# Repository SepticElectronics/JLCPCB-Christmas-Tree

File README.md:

# JLCPCB-Christmas-Tree

This is my entry for the JLCPCB.com Christmas Challenge.

It is a PCB christmas tree assembled from three separate PCBs: one for the Top, on as a spacer and one as the backside.
They are held together by soldering with solder paste on the inside and a hole for a string at the top.

On the inside, there are multiple sideview LEDs to illuminate the edge of the tree. To reduce current consumption, all LEDs are pulse-width-modulated by a PIC16F18344.

The other LEDs are normal topview LEDs, placed on both the top and the bottom side of the tree, which illuminate the tree decorations of the opposing PCB. These LEDs are multiplexed by the MCU, to enable different flashing modes.
These modes are selected by a very simple touch-sensor, built into the main PCB.

Power is supplied by a CR1216-cell, held between the PCBs by friction with SMD-resistors to hold it in position. 

A TPS61260 steps up the battery voltage to 3.3 V.

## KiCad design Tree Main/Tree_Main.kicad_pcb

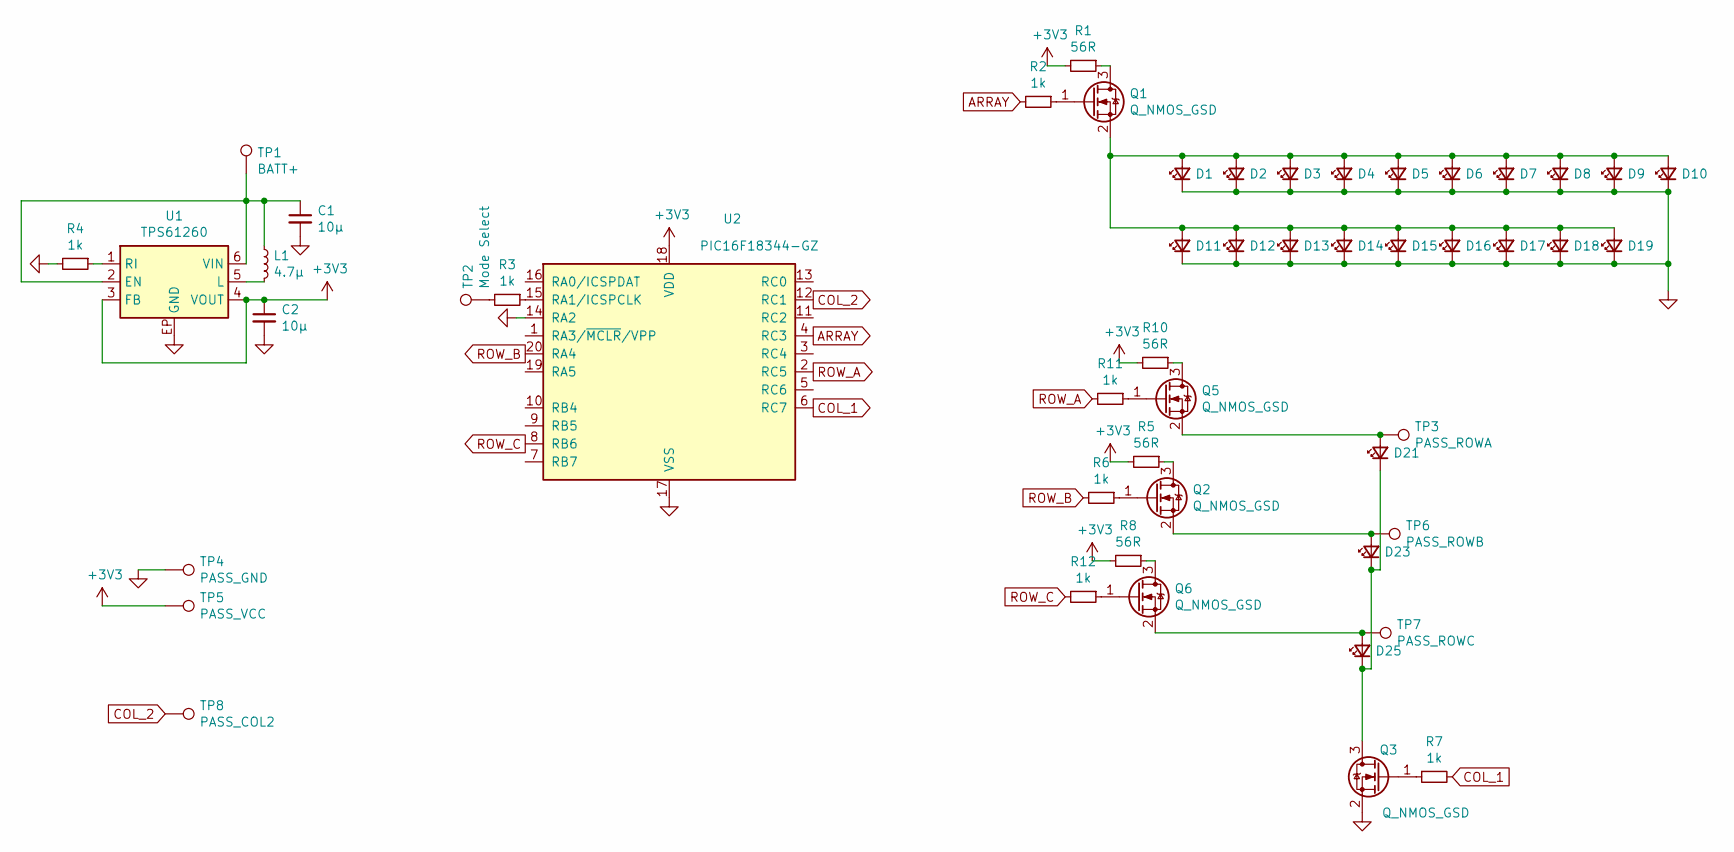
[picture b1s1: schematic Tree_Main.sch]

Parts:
C1, C2: 10µ; C_0603_1608Metric
D1, D2, D3, D4, D5, D6, D7, D8, D9, D10, D11, D12, D13, D14, D15, D16, D17, D18, D19, D21, D23, D25: LED_Small; LED_0603_1608Metric
L1: 4.7µ; L_0805_2012Metric
Q1, Q2, Q3, Q5, Q6: Q_NMOS_GSD; SOT-23
R1, R5, R8, R10: 56R; R_0603_1608Metric
R2, R3, R4, R6, R7, R11, R12: 1k; R_0603_1608Metric
TP1: BATT+; TestPoint_Pad_D4.0mm
TP2: Mode Select; TestPoint_Pad_D4.0mm
TP3: PASS_ROWA; TestPoint_Pad_D1.0mm
TP4: PASS_GND; TestPoint_Pad_D1.0mm
TP5: PASS_VCC; TestPoint_Pad_D1.0mm
TP6: PASS_ROWB; TestPoint_Pad_D1.0mm
TP7: PASS_ROWC; TestPoint_Pad_D1.0mm
TP8: PASS_COL2; TestPoint_Pad_D1.0mm
U1: TPS61260; WSON-6-1EP_2x2mm_P0.65mm_EP1x1.6mm
U2: PIC16F18344-GZ; UQFN-20-1EP_4x4mm_P0.5mm_EP2.8x2.8mm

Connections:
+3V3: C2.1, R1.2, R5.2, R8.2, R10.2, TP5.1, U1.3 (FB), U1.4 (VOUT), U2.18 (VDD)
ARRAY: R2.2, U2.4 (RC3)
COL_1: R7.2, U2.6 (RC7)
COL_2: TP8.1, U2.12 (RC1)
GND: C1.2, C2.2, D1.1 (K), D2.1 (K), D3.1 (K), D4.1 (K), D5.1 (K), D6.1 (K), D7.1 (K), D8.1 (K), D9.1 (K), D10.1 (K), D11.1 (K), D12.1 (K), D13.1 (K), D14.1 (K), D15.1 (K), D16.1 (K), D17.1 (K), D18.1 (K), D19.1 (K), Q3.2 (S), R4.2, TP4.1, U1.EP (GND), U2.14 (RA2), U2.17 (VSS)
unnamed: C1.1, L1.1, TP1.1, U1.2 (EN), U1.6 (VIN)
unnamed: D1.2 (A), D2.2 (A), D3.2 (A), D4.2 (A), D5.2 (A), D6.2 (A), D7.2 (A), D8.2 (A), D9.2 (A), D10.2 (A), D11.2 (A), D12.2 (A), D13.2 (A), D14.2 (A), D15.2 (A), D16.2 (A), D17.2 (A), D18.2 (A), D19.2 (A), Q1.2 (S)
unnamed: D21.2 (A), Q5.2 (S), TP3.1
unnamed: D21.1 (K), D23.1 (K), D25.1 (K), Q3.3 (D)
unnamed: D23.2 (A), Q2.2 (S), TP6.1
unnamed: D25.2 (A), Q6.2 (S), TP7.1
unnamed: L1.2, U1.5 (L)
unnamed: Q1.1 (G), R2.1
unnamed: Q1.3 (D), R1.1
unnamed: Q2.1 (G), R6.1
unnamed: Q2.3 (D), R5.1
unnamed: Q3.1 (G), R7.1
unnamed: Q5.1 (G), R11.1
unnamed: Q5.3 (D), R10.1
unnamed: Q6.1 (G), R12.1
unnamed: Q6.3 (D), R8.1
unnamed: R3.1, U2.15 (RA1/ICSPCLK)
unnamed: R3.2, TP2.1
unnamed: R4.1, U1.1 (RI)
ROW_A: R11.2, U2.2 (RC5)
ROW_B: R6.2, U2.20 (RA4)
ROW_C: R12.2, U2.8 (RB6)

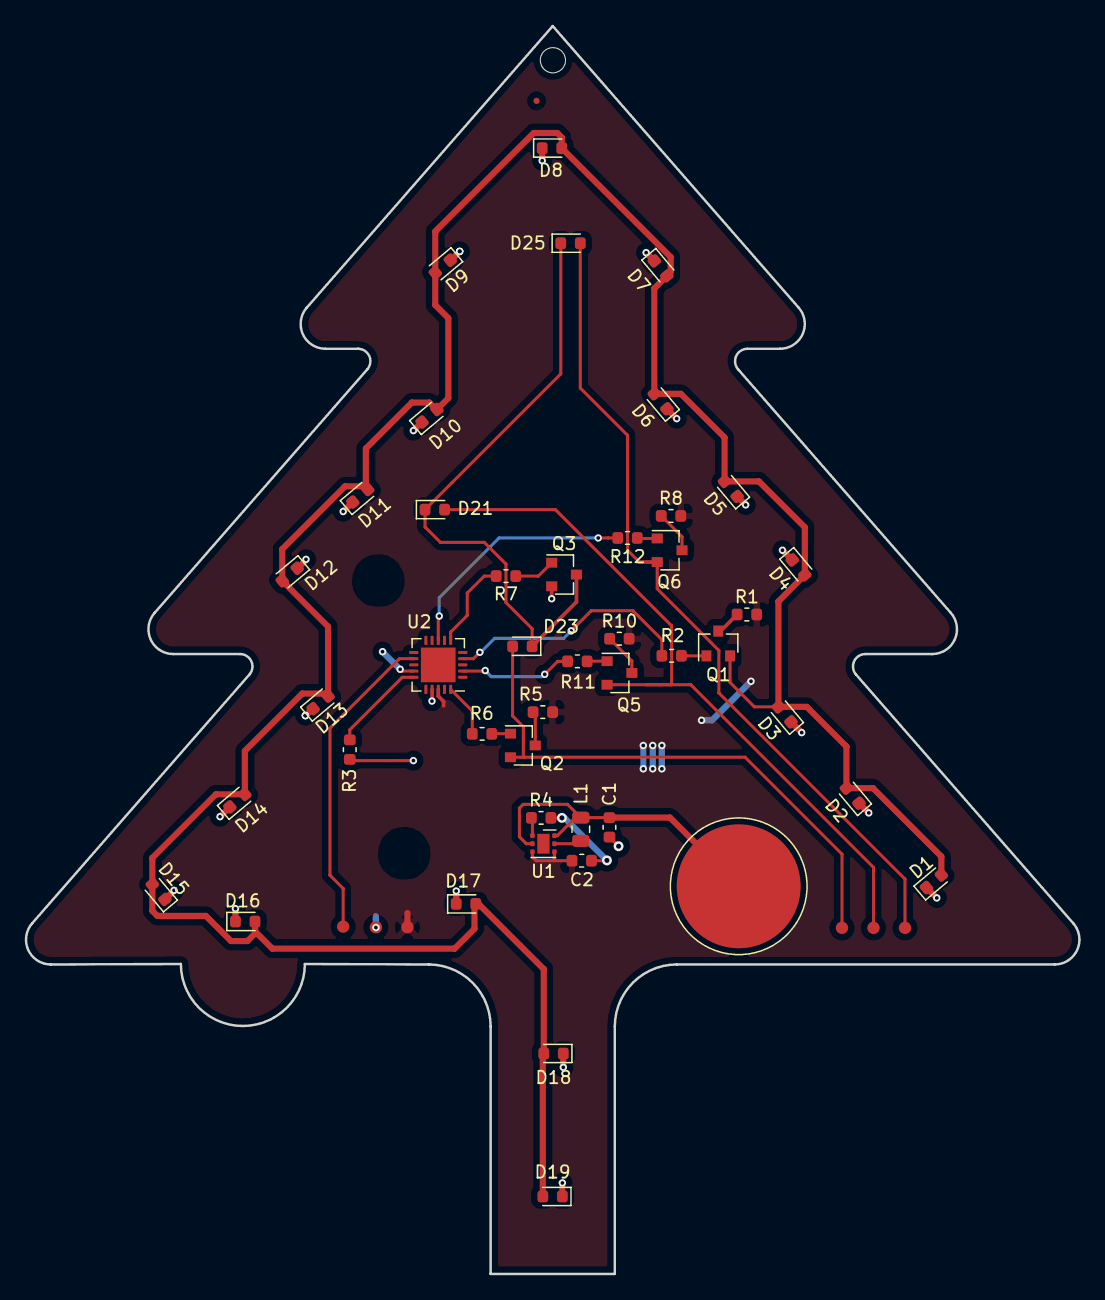
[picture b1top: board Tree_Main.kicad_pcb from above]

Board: 2 copper layers, 85.0 x 100.7 mm, 51 parts (1 on the bottom side), 27 nets.

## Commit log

2020-12-19 Rename Tree_Main.pro to Tree Main/Tree_Main.pro
2020-12-19 Create f
